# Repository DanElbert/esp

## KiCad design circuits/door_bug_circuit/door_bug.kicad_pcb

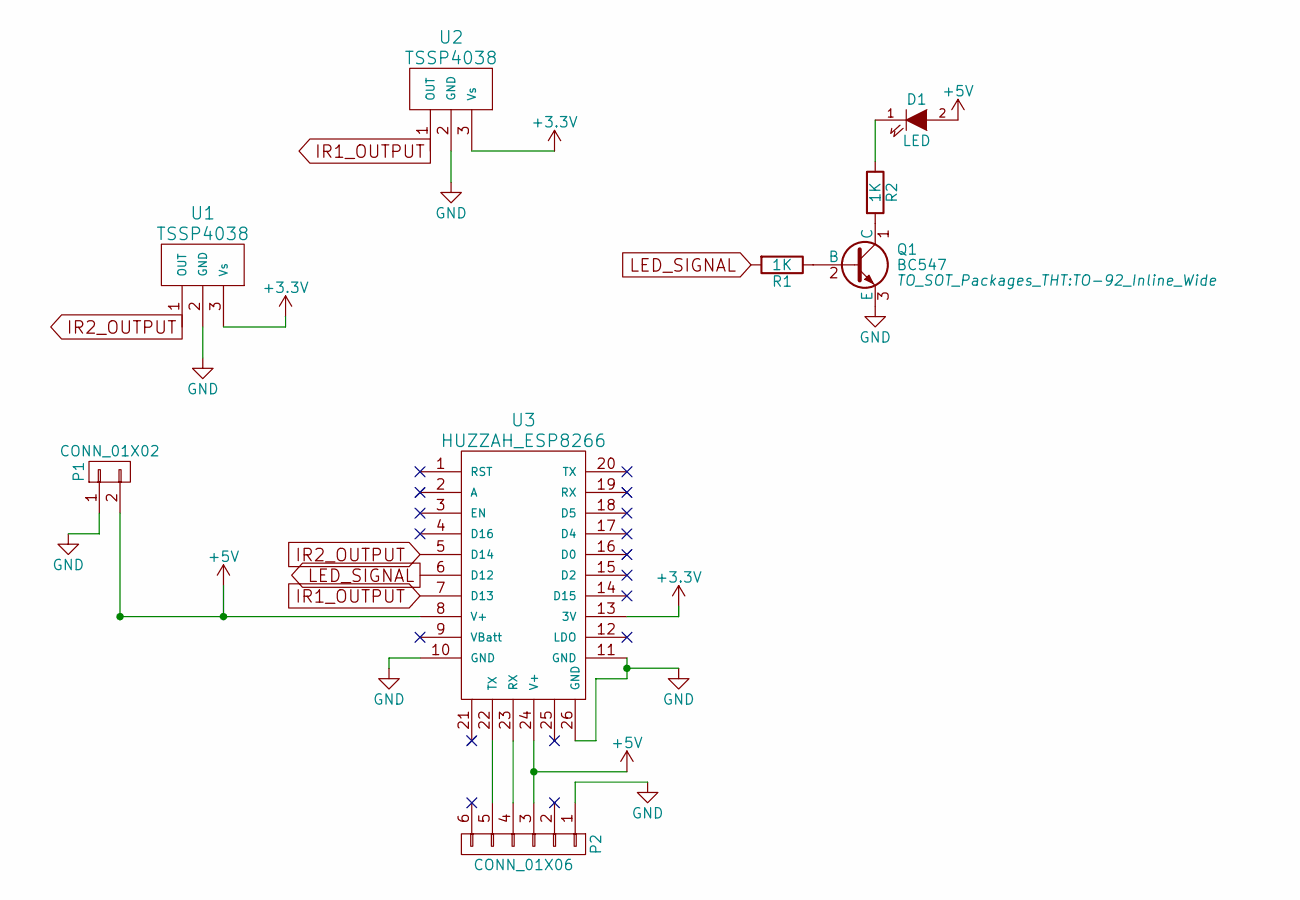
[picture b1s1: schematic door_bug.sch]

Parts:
D1: LED; LED-5MM
P1: CONN_01X02; Socket_Strip_Straight_1x02
P2: CONN_01X06; Pin_Header_Straight_1x06
Q1: BC547; TO-92_Inline_Wide
R1, R2: 1K; Resistor_Horizontal_RM10mm
U1, U2: TSSP4038; TSSP4038_Horizontal
U3: HUZZAH_ESP8266; Huzzah_ESP8266

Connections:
+3V3: U1.3 (Vs), U2.3 (Vs), U3.13 (3V)
+5V: D1.2 (A), P1.2, P2.3, U3.8 (V+), U3.24 (V+)
GND: P1.1, P2.1, Q1.3 (E), U1.2 (GND), U2.2 (GND), U3.10 (GND), U3.11 (GND), U3.26 (GND)
IR1_OUTPUT: U2.1 (OUT), U3.7 (D13)
IR2_OUTPUT: U1.1 (OUT), U3.5 (D14)
LED_SIGNAL: R1.2, U3.6 (D12)
unnamed: D1.1 (K), R2.1
unnamed: P2.4, U3.23 (RX)
unnamed: P2.5, U3.22 (TX)
unnamed: Q1.1 (C), R2.2
unnamed: Q1.2 (B), R1.1

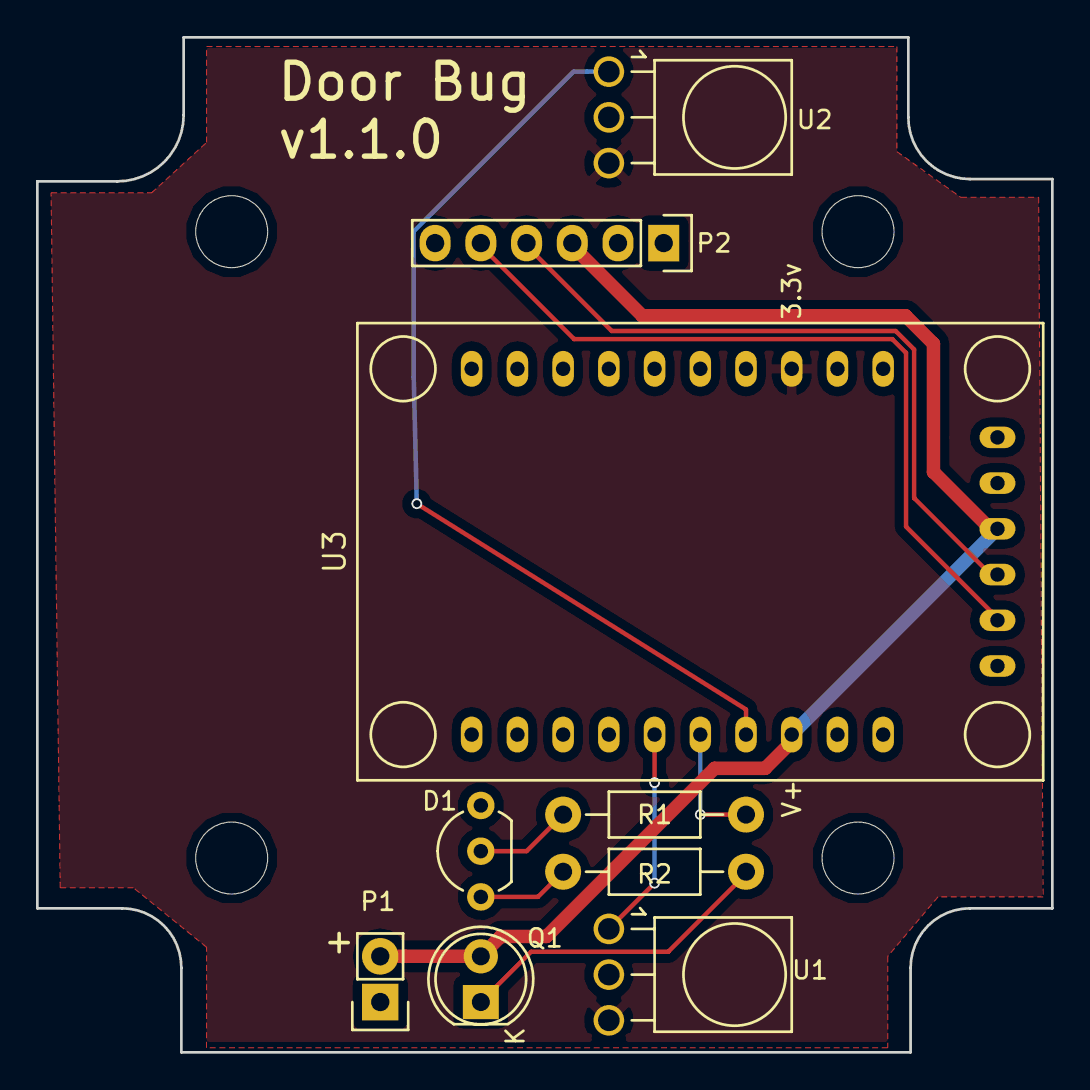
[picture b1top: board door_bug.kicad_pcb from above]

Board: 2 copper layers, 56.4 x 56.4 mm, 9 parts (0 on the bottom side), 11 nets.

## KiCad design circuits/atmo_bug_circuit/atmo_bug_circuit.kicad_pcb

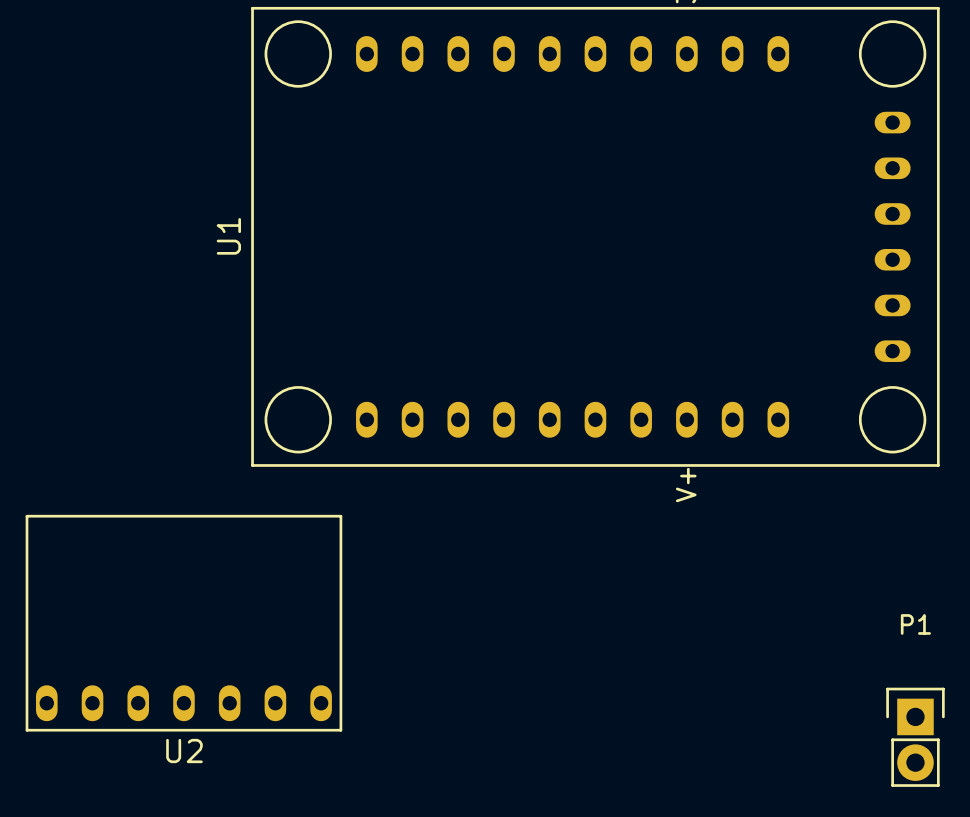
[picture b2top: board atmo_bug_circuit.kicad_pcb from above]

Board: 2 copper layers, 3 parts (0 on the bottom side), 5 nets, no tracks yet.

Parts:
P1: CONN_01X02; Pin_Header_Straight_1x02
U1: HUZZAH_ESP8266; Huzzah_ESP8266
U2: SHT31-DIS_Breakout; SHT31-D

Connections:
3.3V: U1.13, U2.1
5V: P1.1, U1.8
GND: P1.2, U1.10, U1.11, U2.2
SCL: U1.18, U2.3
SDA: U1.17, U2.4

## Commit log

2017-07-13 set up submodules
2017-07-13 added secrets library
2017-07-13 secrets
2017-07-15 init bbq bug
2017-07-18 bbq bug work
2017-07-18 Removed adc lib
2017-07-18 Added max31850 libs
2017-07-19 Working 31850s
2017-07-19 bbq_bug work
2017-07-19 esp bug library work
2017-07-21 bbq bug
2017-08-03 bbq work
2017-08-16 Added circuits
2017-08-16 atmo bug board
2017-12-03 updated door bug
2020-04-03 update submodules
2020-04-03 update atmo_bug
